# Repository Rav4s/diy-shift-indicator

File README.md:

# K-Line (ISO9141) Shift Indicator
A DIY shift indicator for manual transmission cars like my Mazda MX-5 with a K-Line (ISO9141) OBDII interface. The device uses a series of LEDs that illuminate based on engine speed (RPM) to help the driver know when to shift gears in high-pressure situations. My technical writeup for this project, which includes rationale, insight into my design/development process, and future plans can be found [here](https://drive.google.com/file/d/1h4sEP5iF2pkmRt12-wAFUMqSv9QvsOz3/view). Additionally, here are videos of the [startup sequence](https://drive.google.com/file/d/1yGfBQFOaLi5DHMowFaSR_DUKHt-pPL1-/view?usp=sharing) and the [device in action](https://drive.google.com/file/d/1uUzjxnDBYHzpRwuf0LmYo11RxKfqu849/view?usp=sharing).  

## Features
- Displays engine RPM using a set of seven LEDs
- Has three distinct LED colors to show progression from low to high RPM (green -> blue -> red)
- Begins illuminating LEDs at the lower end of shift range (3.5k) and fully illuminates by the higher end (6k), with equal steps in between
- Mounts to the dashboard without significantly obstructing the driver's view of the road
- Doesn't require any modifications to wiring/electronics of the car (plug-and-play)

## Files
The file structure of this repository is as follows: 

```
diy-shift-indicator
│   K-Line (ISO 9141) Shift Indicator Writeup.pdf -- technical writeup on design/development process and future plans
│   LICENSE
│   README.md
│
├───Code -- all Arduino code
│   ├───arduino_obd_reader_display -- code for polling and displaying RPM using LED series
│   │       arduino_obd_reader_display.ino -- handles initialization/communication over LIN bus
│   │       LED_driver.ino -- defines functions to drive and reset LEDs, provides displayRPM functionality
│   │
│   ├───LED_test -- tester sketch to ensure LED series is working
│   │       LED_test.ino
│   │
│   └───modified_iso9141_library -- modified version of the OBD9141 Arduino library used in display program
│           OBD9141.cpp
│           OBD9141.h
│
├───Debug -- Saleae logic analyzer capture files, useful for debugging initialization/connection with ECU
│       First_Success_TX_and_KLINE_Logic.sal
│       RX_Logic.sal
│       TX_and_KLINE_Logic.sal
│       TX_Logic.sal
│
└───Design -- CAD/design files from the prototyping process
    │   Device BOM.xlsx -- full bill of materials for the final product (PCB, boards, wiring, enclosure, etc.)
    │
    ├───Electronics -- breadboard, schematic, and PCB design files
    │   ├───Fritzing (Breadboard)
    │   │       Prototype Design.fzz -- breadboard setup designed for original prototype/testbed
    │   │       SN65HVDA195 IC Part.fzz -- custom Fritzing part designed for LIN transceiver IC
    │   │
    │   └───KiCad (PCB)
    │       └───Shift_Indicator_PCB
    │           │   freerouting.dsn
    │           │   Shift_Indicator_PCB.kicad_pcb -- PCB design for final product, can be exported to Gerbers for fabrication
    │           │   Shift_Indicator_PCB.kicad_pcb.zip
    │           │   Shift_Indicator_PCB.kicad_prl
    │           │   Shift_Indicator_PCB.kicad_pro
    │           │   Shift_Indicator_PCB.kicad_sch -- schematic defining all electrical connections for PCB
    │           │   Shift_Indicator_PCB.net -- netlist used to transfer schematic data to PCB design
    │           │   Shift_Indicator_PCB_BOM.csv -- bill of materials for PCB
    │
    └───Mechanics -- enclosure/lid design files
            Enclosure.3mf -- Bambu slicer file for 3D printing enclosure and lid
            Enclosure.stl -- CAD design for device enclosure, can be mounted to car dashboard 
            Lid.stl -- CAD design for lid for the enclosure
```

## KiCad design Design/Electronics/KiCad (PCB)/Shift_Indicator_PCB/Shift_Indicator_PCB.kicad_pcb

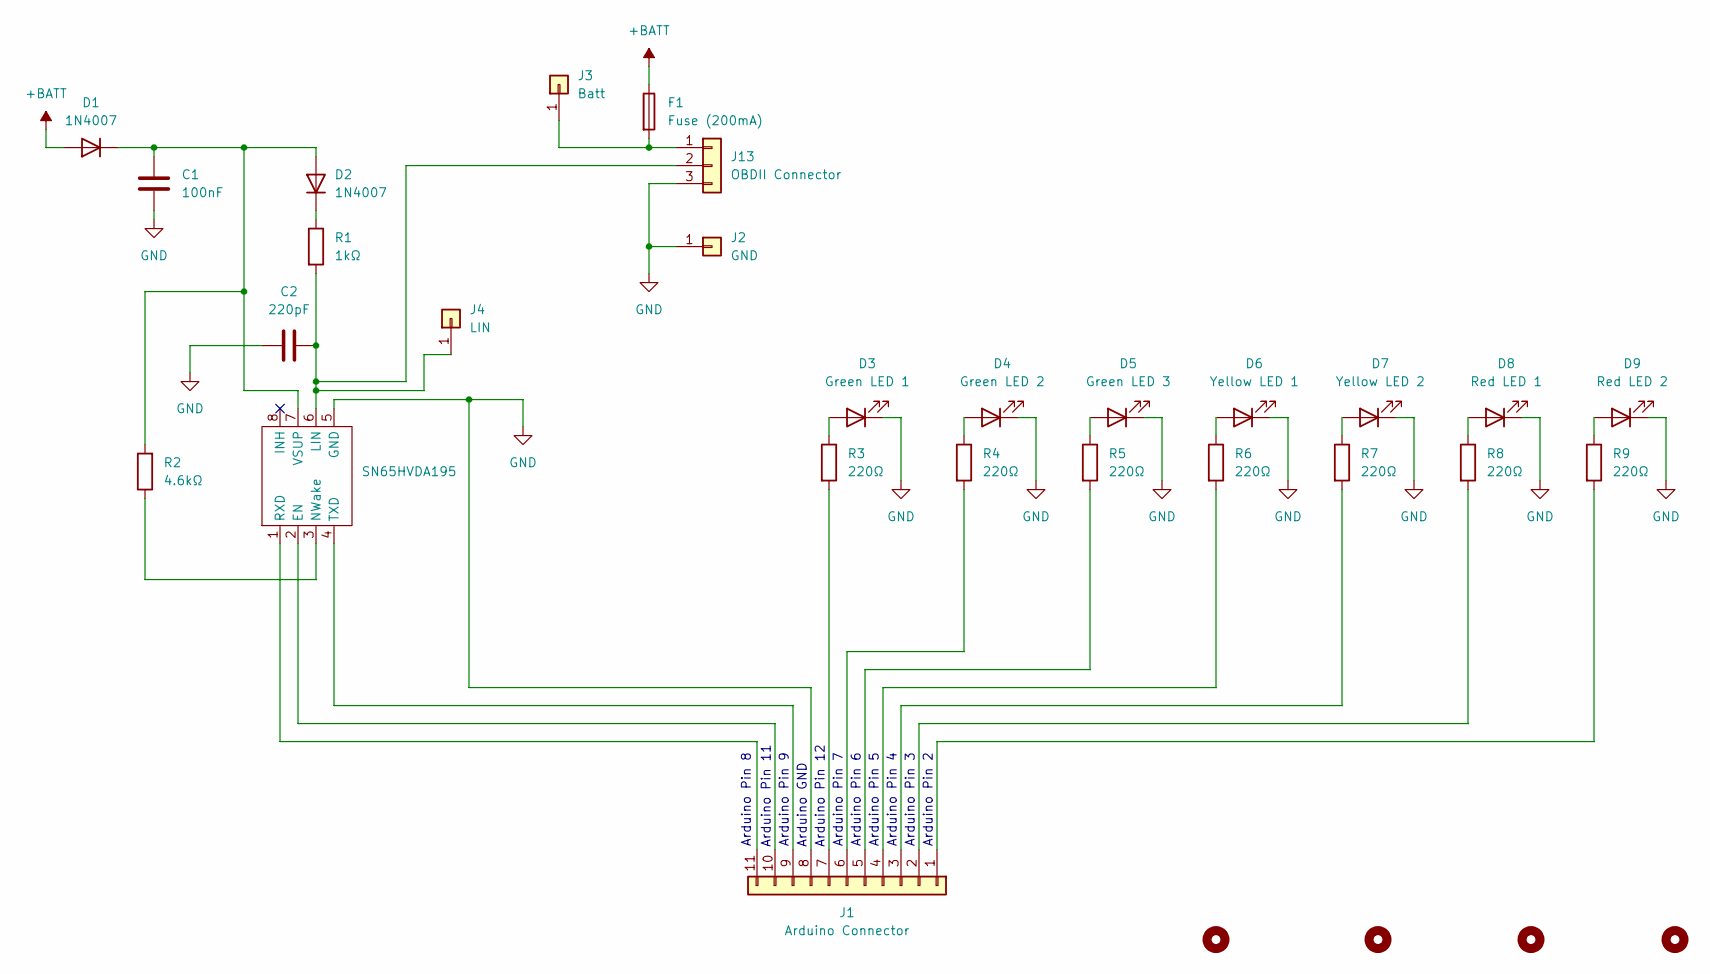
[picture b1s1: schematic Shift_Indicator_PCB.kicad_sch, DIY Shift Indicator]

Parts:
C1: 100nF; C_0805_2012Metric_Pad1.18x1.45mm_HandSolder
C2: 220pF; C_0805_2012Metric_Pad1.18x1.45mm_HandSolder
D1, D2: 1N4007; D_DO-41_SOD81_P10.16mm_Horizontal
D3: Green LED 1; LED_D1.8mm_W3.3mm_H2.4mm
D4: Green LED 2; LED_D1.8mm_W3.3mm_H2.4mm
D5: Green LED 3; LED_D1.8mm_W3.3mm_H2.4mm
D6: Yellow LED 1; LED_D1.8mm_W3.3mm_H2.4mm
D7: Yellow LED 2; LED_D1.8mm_W3.3mm_H2.4mm
D8: Red LED 1; LED_D1.8mm_W3.3mm_H2.4mm
D9: Red LED 2; LED_D1.8mm_W3.3mm_H2.4mm
F1: Fuse (200mA); Fuseholder_Cylinder-5x20mm_Stelvio-Kontek_PTF78_Horizontal_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
H1, H2, H3, H4: MountingHole; MountingHole_3.2mm_M3_Pad
J1: Arduino Connector; PinSocket_1x11_P2.54mm_Vertical
J2: GND; PinHeader_1x01_P2.54mm_Vertical
J3: Batt; PinHeader_1x01_P2.54mm_Vertical
J4: LIN; PinHeader_1x01_P2.54mm_Vertical
J13: OBDII Connector; PinSocket_1x03_P2.54mm_Vertical
R1: 1kΩ; R_0805_2012Metric_Pad1.20x1.40mm_HandSolder
R2: 4.6kΩ; R_0805_2012Metric_Pad1.20x1.40mm_HandSolder
R3, R4, R5, R6, R7, R8, R9: 220Ω; R_0805_2012Metric_Pad1.20x1.40mm_HandSolder
SN65HVDA195: SOIC-8_3.9x4.9mm_P1.27mm

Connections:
+BATT: D1.2 (A), F1.1
GND: C1.2, C2.1, D3.1 (K), D4.1 (K), D5.1 (K), D6.1 (K), D7.1 (K), D8.1 (K), D9.1 (K), J1.8, J2.1, J13.3, SN65HVDA195.5 (GND)
unnamed: C1.1, D1.1 (K), D2.2 (A), R2.2, SN65HVDA195.7 (VSUP)
unnamed: D2.1 (K), R1.1
unnamed: D3.2 (A), R3.1
unnamed: D4.2 (A), R4.1
unnamed: D5.2 (A), R5.1
unnamed: D6.2 (A), R6.1
unnamed: D7.2 (A), R7.1
unnamed: D8.2 (A), R8.1
unnamed: D9.2 (A), R9.1
unnamed: J1.1, R9.2
unnamed: J1.2, R8.2
unnamed: J1.3, R7.2
unnamed: J1.4, R6.2
unnamed: J1.5, R5.2
unnamed: J1.6, R4.2
unnamed: J1.7, R3.2
unnamed: J1.9, SN65HVDA195.4 (TXD)
unnamed: J1.10, SN65HVDA195.2 (EN)
unnamed: J1.11, SN65HVDA195.1 (RXD)
unnamed: F1.2, J3.1, J13.1
unnamed: C2.2, J4.1, J13.2, R1.2, SN65HVDA195.6 (LIN)
unnamed: R2.1, SN65HVDA195.3 (NWake)

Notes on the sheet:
Arduino Pin 12
Arduino Pin 8
Arduino Pin 2
Arduino GND
Arduino Pin 11
Arduino Pin 3
Arduino Pin 4
Arduino Pin 6
Arduino Pin 5
Arduino Pin 7
Arduino Pin 9

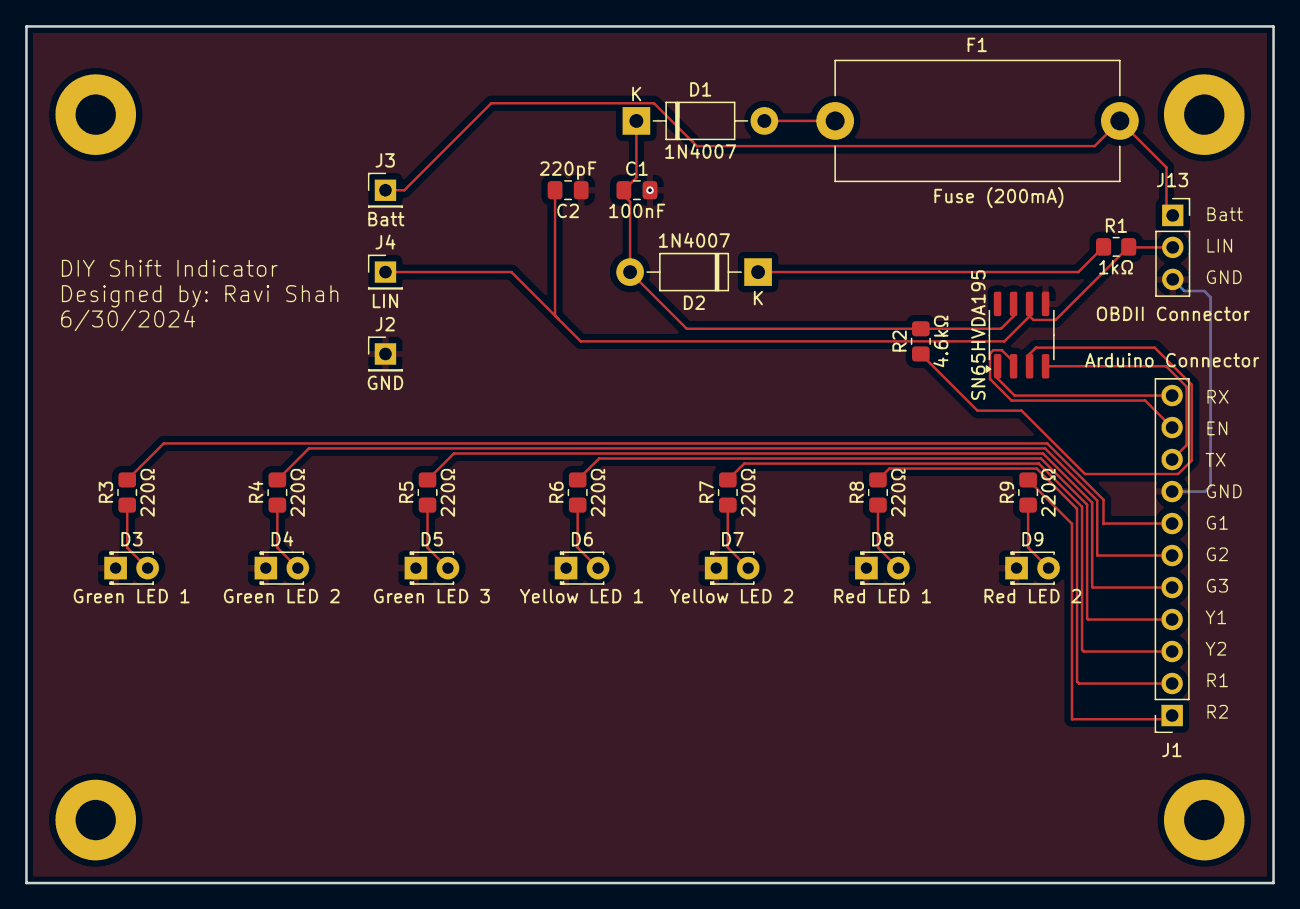
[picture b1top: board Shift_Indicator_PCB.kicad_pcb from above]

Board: 2 copper layers, 99.0 x 68.0 mm, 31 parts (0 on the bottom side), 24 nets.

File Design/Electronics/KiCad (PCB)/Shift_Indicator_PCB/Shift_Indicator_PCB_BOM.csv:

"Id;""Designator"";""Footprint"";""Quantity"";""Designation"";""Supplier and ref"";,,,,,,"
"1;""J4"";""PinHeader_1x01_P2.54mm_Vertical"";1;""LIN"";;;,,,,,,"
"2;""J3"";""PinHeader_1x01_P2.54mm_Vertical"";1;""Batt"";;;,,,,,,"
"3;""J2"";""PinHeader_1x01_P2.54mm_Vertical"";1;""GND"";;;,,,,,,"
"4;""F1"";""Fuseholder_Cylinder-5x20mm_Stelvio-Kontek_PTF78_Horizontal_Open"";1;""Fuse (200mA)"";;;,,,,,,"
"5;""D9"";""LED_D1.8mm_W3.3mm_H2.4mm"";1;""Red LED 2"";;;,,,,,,"
"6;""D8"";""LED_D1.8mm_W3.3mm_H2.4mm"";1;""Red LED 1"";;;,,,,,,"
"7;""D7"";""LED_D1.8mm_W3.3mm_H2.4mm"";1;""Yellow LED 2"";;;,,,,,,"
"8;""D6"";""LED_D1.8mm_W3.3mm_H2.4mm"";1;""Yellow LED 1"";;;,,,,,,"
"9;""D5"";""LED_D1.8mm_W3.3mm_H2.4mm"";1;""Green LED 3"";;;,,,,,,"
"10;""D4"";""LED_D1.8mm_W3.3mm_H2.4mm"";1;""Green LED 2"";;;,,,,,,"
"11;""D3"";""LED_D1.8mm_W3.3mm_H2.4mm"";1;""Green LED 1"";;;,,,,,,"
"12;""R9,R8,R7,R6,R5,R4,""R3"""";""""R_0805_2012Metric_Pad1.20x1.40mm_HandSolder"""";7;""""220Ω"""";;;"""
"13;""R2"";""R_0805_2012Metric_Pad1.20x1.40mm_HandSolder"";1;""4.6kΩ"";;;,,,,,,"
"14;""R1"";""R_0805_2012Metric_Pad1.20x1.40mm_HandSolder"";1;""1kΩ"";;;,,,,,,"
"15;""C2"";""C_0805_2012Metric_Pad1.18x1.45mm_HandSolder"";1;""220pF"";;;,,,,,,"
"16;""C1"";""C_0805_2012Metric_Pad1.18x1.45mm_HandSolder"";1;""100nF"";;;,,,,,,"
"17;""J13"";""PinSocket_1x03_P2.54mm_Vertical"";1;""OBDII Connector"";;;,,,,,,"
"18;""J1"";""PinSocket_1x11_P2.54mm_Vertical"";1;""Arduino Connector"";;;,,,,,,"
"19;""SN65HVDA195"";""SOIC-8_3.9x4.9mm_P1.27mm"";1;""~"";;;,,,,,,"
"20;""D2,""D1"""";""""D_DO-41_SOD81_P10.16mm_Horizontal"""";2;""""1N4007"""";;;"",,,,,"

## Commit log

2024-05-18 Added initial prototype design file
2024-05-18 Add k-line and OBDII connector
2024-05-20 Update readme with file list
2024-05-22 Added prototype connections for buck converter
2024-06-04 Update proto
2024-06-04 create custom part for SN65HVDA195 IC
2024-06-04 update circuit designs with IC implementation
2024-06-04 folderize
2024-06-04 testing example reader code
2024-06-05 update reader code
2024-06-13 update pins to match board
2024-06-13 Added LED test code
2024-06-24 Added debug captures from Saleae logic analyzer
2024-06-24 refresh files
2024-06-27 FINALLY IT WORKS
2024-06-27 placeholder for modification to iso9141 library
2024-06-27 change pins to correct ones for altsoftserial
2024-06-27 add value for serial timeout
2024-06-28 todo
2024-06-28 fix newline
2024-06-28 reorganize and add KiCad project
2024-06-28 make RPM work and note to self
2024-06-29 cleanup and format
2024-06-29 add file shell for LED driver
2024-06-29 add code for startup and seven display options
2024-06-30 Add proper RPM values
2024-06-30 first half of schematic
2024-07-01 add gitignore for kicad
2024-07-01 add LED display on schematic
2024-07-01 in right place?
2024-07-01 refresh
2024-07-01 schematic: added proper connectors for OBDII and Arduino
2024-07-02 added first iteration of PCB
2024-07-03 fix PCB for approval + netlist/BOM
2024-07-04 add all DigiKey part numbers to BOM
2024-07-14 fix to working pin
2024-07-15 change pin for testing
2024-07-15 lowered RPM ranges for activation
2024-07-16 created cad models for enclosure and lid
2024-07-16 chamfer front edges on enclosure
2024-07-17 add modified iso9141 library
2024-07-18 add bambu slicer file
2024-07-18 add full device BOM
2024-07-19 todos done
2024-07-19 add comments to main loop
2024-07-19 comment displayRPM function
2024-07-22 Added writeup for documentation
2024-07-23 Update README.md
    - Added folder structure
    - Added link to technical writeup
    - Added some todos
2024-07-23 Add explanations for file structure
2024-07-23 add summary and feature list
2024-07-24 Add links to videos of device
2024-07-25 arrows
